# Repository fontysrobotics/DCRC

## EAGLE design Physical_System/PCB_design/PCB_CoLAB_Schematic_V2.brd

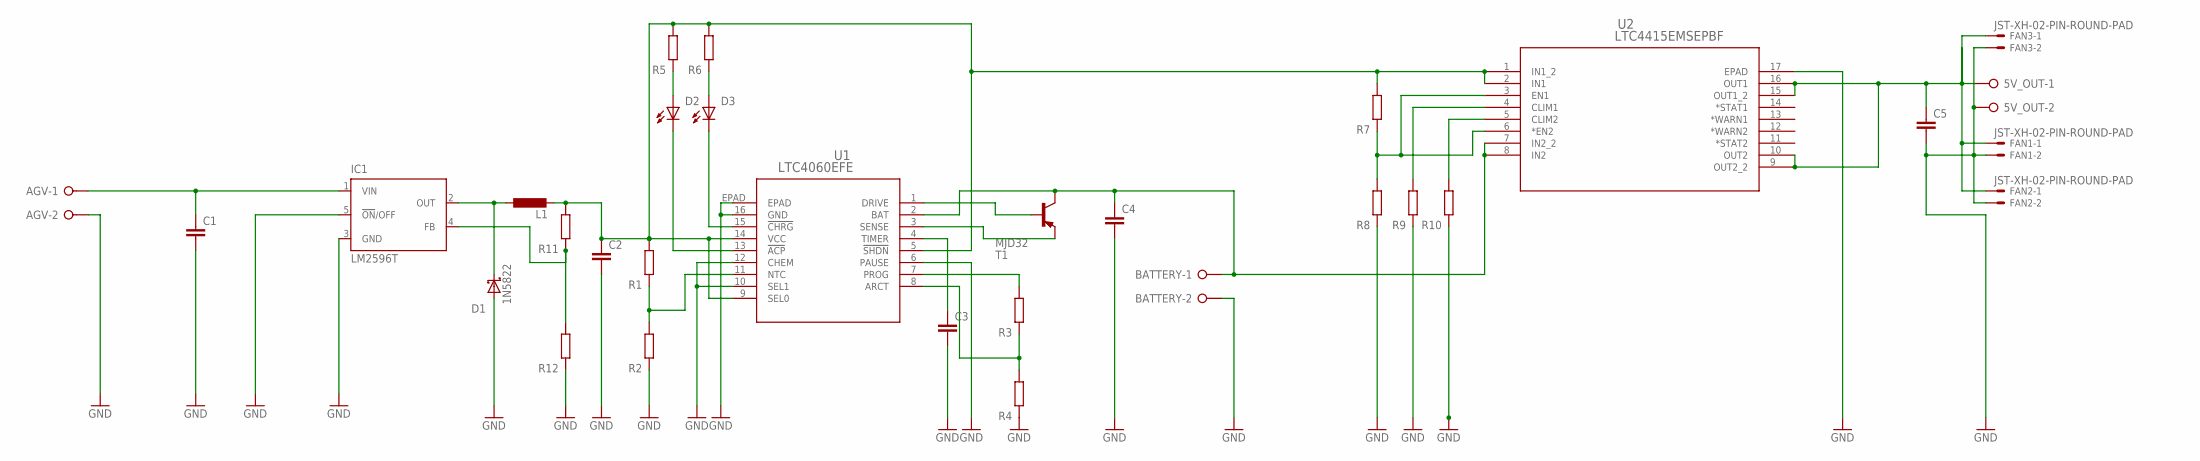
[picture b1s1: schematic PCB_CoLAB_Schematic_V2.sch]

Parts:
5V_OUT: W237-02P; W237-132
AGV: W237-02P; W237-132
BATTERY: W237-02P; W237-132
C1: C-EU050-075X075; C050-075X075
C2: C-EU025-050X050; C025-050X050
C3, C5: C-EU025-024X044; C025-024X044
C4: C-EU050-050X075; C050-050X075
D1: 1N5822; DIOAD2120W130L950D530P
D2, D3: LED_ELD260; LED_LD260
FAN1, FAN2, FAN3: JST-XH-02-PIN-ROUND-PAD; JST-XH-02-PACKAGE-ROUND-PAD
IC1: LM2596T; T05D
L1: L-EU0204/7; 0204/7
R1, R2, R3, R4, R5, R6, R7, R8, R9, R10, R11, R12: R0204/7; 0204/7
T1: MJD32; DPAK
U1: LTC4060EFE; TSSOP-16_FE/BC_LIT
U2: LTC4415EMSEPBF; MSOP-16_MSE

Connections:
GND: 5V_OUT.2, AGV.2, BATTERY.2, C1.2, C2.2, C3.2, C4.2, C5.2, D1.A, FAN1.2, FAN2.2, FAN3.2, IC1.3 (GND), IC1.5 (!ON!/OFF), R2.1, R4.1, R8.1, R9.1, R10.1, R12.1, U1.6 (PAUSE), U1.10 (SEL1), U1.12 (CHEM), U1.16 (GND), U1.EPAD, U2.17 (EPAD)
unnamed: R3.2, U1.7 (PROG)
unnamed: AGV.1, C1.1, IC1.1 (VIN)
unnamed: D1.C, IC1.2 (OUT), L1.1
unnamed: R1.1, R2.2, U1.11 (NTC)
unnamed: R7.1, R8.2, U2.3 (EN1), U2.6 (*EN2)
unnamed: R3.1, R4.2, U1.8 (ARCT)
unnamed: T1.3 (E), U1.3 (SENSE)
unnamed: T1.1 (B), U1.1 (DRIVE)
unnamed: C2.1, L1.2, R1.2, R5.2, R6.2, R7.2, R11.2, U1.5 (!SHDN), U1.9 (SEL0), U1.14 (VCC), U2.1 (IN1_2), U2.2 (IN1)
unnamed: C3.1, U1.4 (TIMER)
unnamed: D2.A, R5.1
unnamed: D2.K (C), U1.13 (!ACP)
unnamed: D3.K (C), U1.15 (!CHRG)
unnamed: D3.A, R6.1
unnamed: BATTERY.1, C4.1, T1.4 (C), U1.2 (BAT), U2.7 (IN2_2), U2.8 (IN2)
unnamed: R9.2, U2.4 (CLIM1)
unnamed: R10.2, U2.5 (CLIM2)
unnamed: 5V_OUT.1, C5.1, FAN1.1, FAN2.1, FAN3.1, U2.9 (OUT2_2), U2.10 (OUT2), U2.15 (OUT1_2), U2.16 (OUT1)
unnamed: IC1.4 (FB), R11.1, R12.2

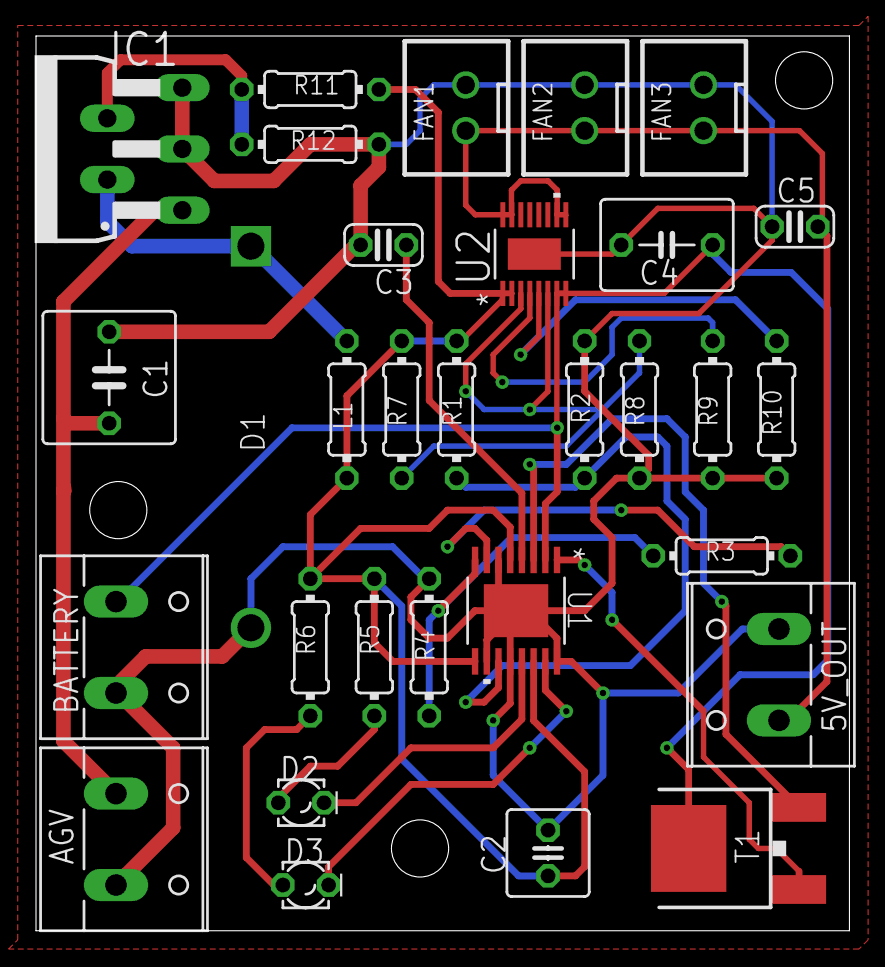
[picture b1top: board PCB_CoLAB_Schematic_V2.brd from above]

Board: 2 copper layers, 45.2 x 49.7 mm, 31 parts (1 on the bottom side), 20 nets.

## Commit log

2021-06-11 initialization
2021-06-14 Initualize
2021-06-14 responsibilityseparation1
2021-06-16 init blackboard
2021-06-21 emergency stop feature v1
2021-06-22 connection to agv node
2021-06-22 connection to blackboard emergency topic
2021-06-23 lidar subscription
2021-06-23 error resolving
2021-06-23 revert
2021-06-23 robot.py
2021-06-23 client/server basic scripts
2021-06-24 server/client rework
2021-06-24 get task priority from blackboard to robotPi via topics and ssh
2021-06-25 small fixes
2021-06-25 RobotPackage
2021-06-25 robot navigation restructuring & obstacle avoidance basics
2021-06-25 topics message type change
2021-06-25 get preprocessed data via tcp server
2021-06-30 execute task
2021-06-30 emergency stop feature changes
2021-06-30 added uwb code
2021-07-01 ssh robotPose
2021-07-01 tcp server changes
2021-07-01 server changes
2021-07-01 dummy test
2021-07-05 final push
2021-07-05 Custom ros2 message for bridge
2021-07-05 added blackboard_interfaces and restrucured package
2021-07-06 Add files via upload
    Sequence diagrams for safety features
2021-07-06 Add files via upload
    Safety features Reports
2021-07-06 Network wiki
2021-07-06 Networking wiki
2021-07-06 Blackboard wiki
2021-07-06 ROS bridge wiki
